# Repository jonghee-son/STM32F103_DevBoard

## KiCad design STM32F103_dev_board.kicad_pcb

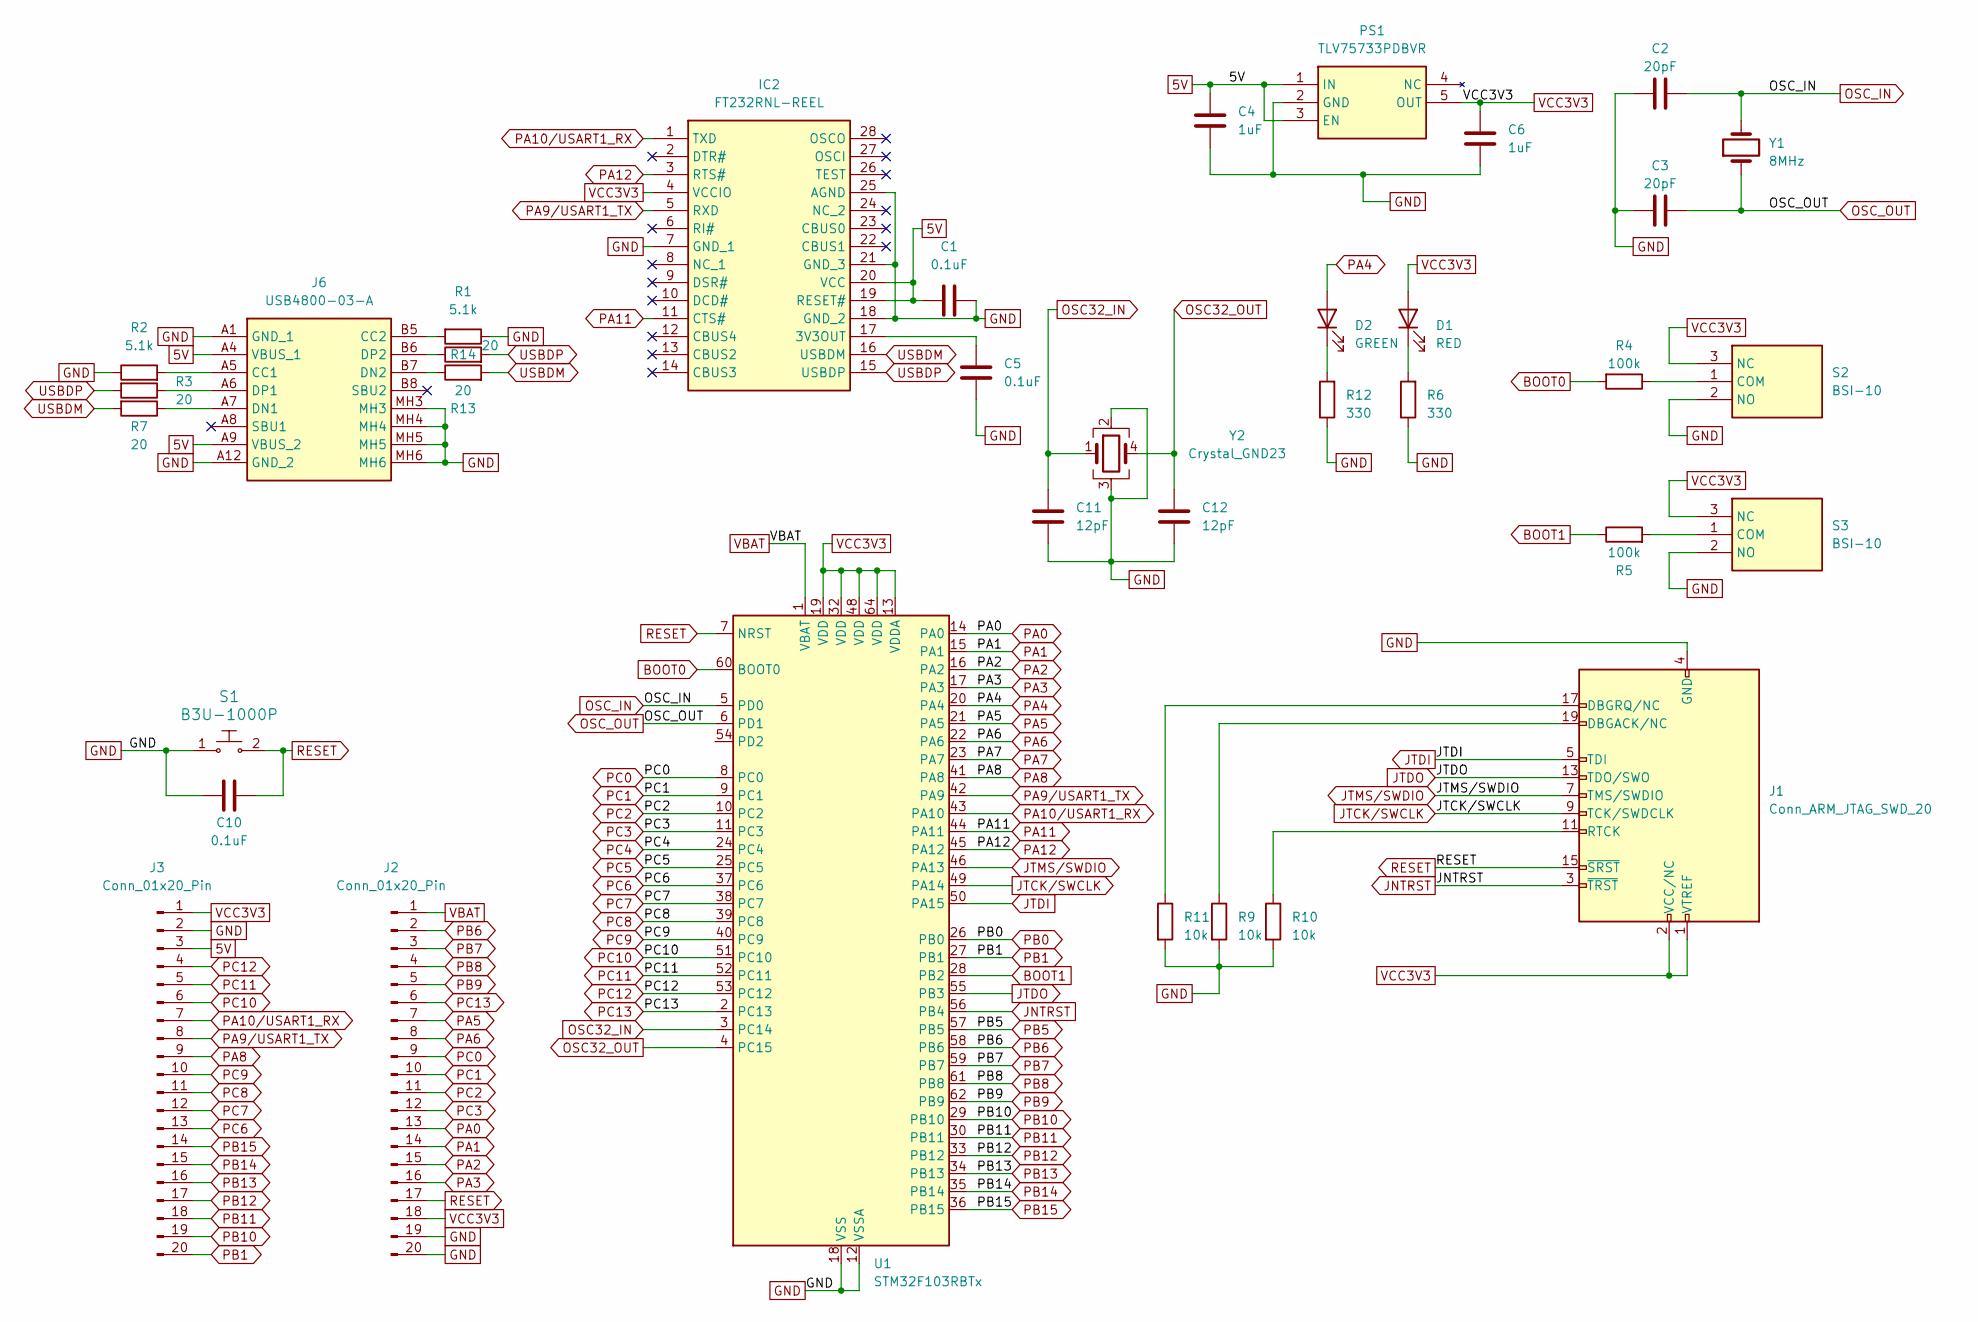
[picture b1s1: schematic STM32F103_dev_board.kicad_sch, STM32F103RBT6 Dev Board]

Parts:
C1, C5, C10: 0.1uF; C_0603_1608Metric_Pad1.08x0.95mm_HandSolder
C2, C3: 20pF; C_0603_1608Metric_Pad1.08x0.95mm_HandSolder
C4, C6: 1uF; C_0603_1608Metric_Pad1.08x0.95mm_HandSolder
C11, C12: 12pF; C_0603_1608Metric_Pad1.08x0.95mm_HandSolder
D1: RED; LED_0603_1608Metric_Pad1.05x0.95mm_HandSolder
D2: GREEN; LED_0603_1608Metric_Pad1.05x0.95mm_HandSolder
IC2: FT232RNL-REEL; SOP65P780X200-28N; Mouser Part Number 895-FT232RNL-REEL
J1: Conn_ARM_JTAG_SWD_20; IDC-Header_2x10_P2.54mm_Vertical
J2, J3: Conn_01x20_Pin; PinHeader_1x20_P2.54mm_Vertical
J6: USB4800-03-A; USB480003A; Mouser Part Number 640-USB4800-03-A
PS1: TLV75733PDBVR; SOT95P280X145-5N; Manufacturer_Part_Number TLV75733PDBVR; Mouser Part Number 595-TLV75733PDBVR
R1, R2: 5.1k; R_0603_1608Metric_Pad0.98x0.95mm_HandSolder
R3, R7, R13, R14: 20; R_0603_1608Metric_Pad0.98x0.95mm_HandSolder
R4, R5: 100k; R_0603_1608Metric_Pad0.98x0.95mm_HandSolder
R6, R12: 330; R_0603_1608Metric_Pad0.98x0.95mm_HandSolder
R9, R10, R11: 10k; R_0603_1608Metric_Pad0.98x0.95mm_HandSolder
S1: B3U-1000P; Switch_Tactile_SMD_B3U-1000P; MPN B3U-1000P; Digi-Key_PN SW1020CT-ND
S2, S3: BSI-10; BSI10; Manufacturer_Part_Number BSI-10
U1: STM32F103RBTx; LQFP-64_10x10mm_P0.5mm
Y1: 8MHz; Crystal_SMD_HC49-SD_HandSoldering
Y2: Crystal_GND23; Crystal_SMD_SeikoEpson_MC306-4Pin_8.0x3.2mm_HandSoldering

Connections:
5V: C1.2, C4.2, IC2.19 (RESET#), IC2.20 (VCC), J3.3, J6.A4 (VBUS_1), J6.A9 (VBUS_2), PS1.1 (IN), PS1.3 (EN)
BOOT0: R4.2, U1.60 (BOOT0)
BOOT1: R5.1, U1.28 (PB2)
GND: C1.1, C2.1, C3.1, C4.1, C5.1, C6.1, C10.2, C11.1, C12.1, IC2.7 (GND_1), IC2.18 (GND_2), IC2.21 (GND_3), IC2.25 (AGND), J1.4 (GND), J1.6 (GND), J1.8 (GND), J1.10 (GND), J1.12 (GND), J1.14 (GND), J1.16 (GND), J1.18 (GND), J1.20 (GND), J2.19, J2.20, J3.2, J6.A1 (GND_1), J6.A12 (GND_2), J6.MH3, J6.MH4, J6.MH5, J6.MH6, PS1.2 (GND), R1.1, R2.1, R6.1, R9.2, R10.2, R11.2, R12.1, S1.1, S2.2 (NO), S3.2 (NO), U1.12 (VSSA), U1.18 (VSS), U1.31 (VSS), U1.47 (VSS), U1.63 (VSS), Y2.2, Y2.3
JNTRST: J1.3 (~TRST), U1.56 (PB4)
JTCK/SWCLK: J1.9 (TCK/SWDCLK), U1.49 (PA14)
JTDI: J1.5 (TDI), U1.50 (PA15)
JTDO: J1.13 (TDO/SWO), U1.55 (PB3)
JTMS/SWDIO: J1.7 (TMS/SWDIO), U1.46 (PA13)
unnamed: D1.1 (K), R6.2
unnamed: D2.1 (K), R12.2
unnamed: C5.2, IC2.17 (3V3OUT)
unnamed: J1.19 (DBGACK/NC), R9.1
unnamed: J1.17 (DBGRQ/NC), R11.1
unnamed: J1.11 (RTCK), R10.1
unnamed: J6.A5 (CC1), R2.2
unnamed: J6.B5 (CC2), R1.2
unnamed: J6.A7 (DN1), R7.1
unnamed: J6.B7 (DN2), R13.1
unnamed: J6.A6 (DP1), R3.1
unnamed: J6.B6 (DP2), R14.1
unnamed: R4.1, S2.1 (COM)
unnamed: R5.2, S3.1 (COM)
OSC32_IN: C11.2, U1.3 (PC14), Y2.1
OSC32_OUT: C12.2, U1.4 (PC15), Y2.4
OSC_IN: C2.2, U1.5 (PD0), Y1.2
OSC_OUT: C3.2, U1.6 (PD1), Y1.1
PA0: J2.13, U1.14 (PA0)
PA1: J2.14, U1.15 (PA1)
PA2: J2.15, U1.16 (PA2)
PA3: J2.16, U1.17 (PA3)
PA4: D2.2 (A), U1.20 (PA4)
PA5: J2.7, U1.21 (PA5)
PA6: J2.8, U1.22 (PA6)
PA7: U1.23 (PA7)
PA8: J3.9, U1.41 (PA8)
PA9/USART1_TX: IC2.5 (RXD), J3.8, U1.42 (PA9)
PA10/USART1_RX: IC2.1 (TXD), J3.7, U1.43 (PA10)
PA11: IC2.11 (CTS#), U1.44 (PA11)
PA12: IC2.3 (RTS#), U1.45 (PA12)
PB0: U1.26 (PB0)
PB1: J3.20, U1.27 (PB1)
PB5: U1.57 (PB5)
PB6: J2.2, U1.58 (PB6)
PB7: J2.3, U1.59 (PB7)
PB8: J2.4, U1.61 (PB8)
PB9: J2.5, U1.62 (PB9)
PB10: J3.19, U1.29 (PB10)
PB11: J3.18, U1.30 (PB11)
PB12: J3.17, U1.33 (PB12)
PB13: J3.16, U1.34 (PB13)
PB14: J3.15, U1.35 (PB14)
PB15: J3.14, U1.36 (PB15)
PC0: J2.9, U1.8 (PC0)
PC1: J2.10, U1.9 (PC1)
PC2: J2.11, U1.10 (PC2)
PC3: J2.12, U1.11 (PC3)
PC4: U1.24 (PC4)
PC5: U1.25 (PC5)
PC6: J3.13, U1.37 (PC6)
PC7: J3.12, U1.38 (PC7)
PC8: J3.11, U1.39 (PC8)
PC9: J3.10, U1.40 (PC9)
PC10: J3.6, U1.51 (PC10)
PC11: J3.5, U1.52 (PC11)
PC12: J3.4, U1.53 (PC12)
PC13: J2.6, U1.2 (PC13)
RESET: C10.1, J1.15 (~SRST), J2.17, S1.2, U1.7 (NRST)
USBDM: IC2.16 (USBDM), R7.2, R13.2
USBDP: IC2.15 (USBDP), R3.2, R14.2
VBAT: J2.1, U1.1 (VBAT)
VCC3V3: C6.2, D1.2 (A), IC2.4 (VCCIO), J1.1 (VTREF), J1.2 (VCC/NC), J2.18, J3.1, PS1.5 (OUT), S2.3 (NC), S3.3 (NC), U1.13 (VDDA), U1.19 (VDD), U1.32 (VDD), U1.48 (VDD), U1.64 (VDD)

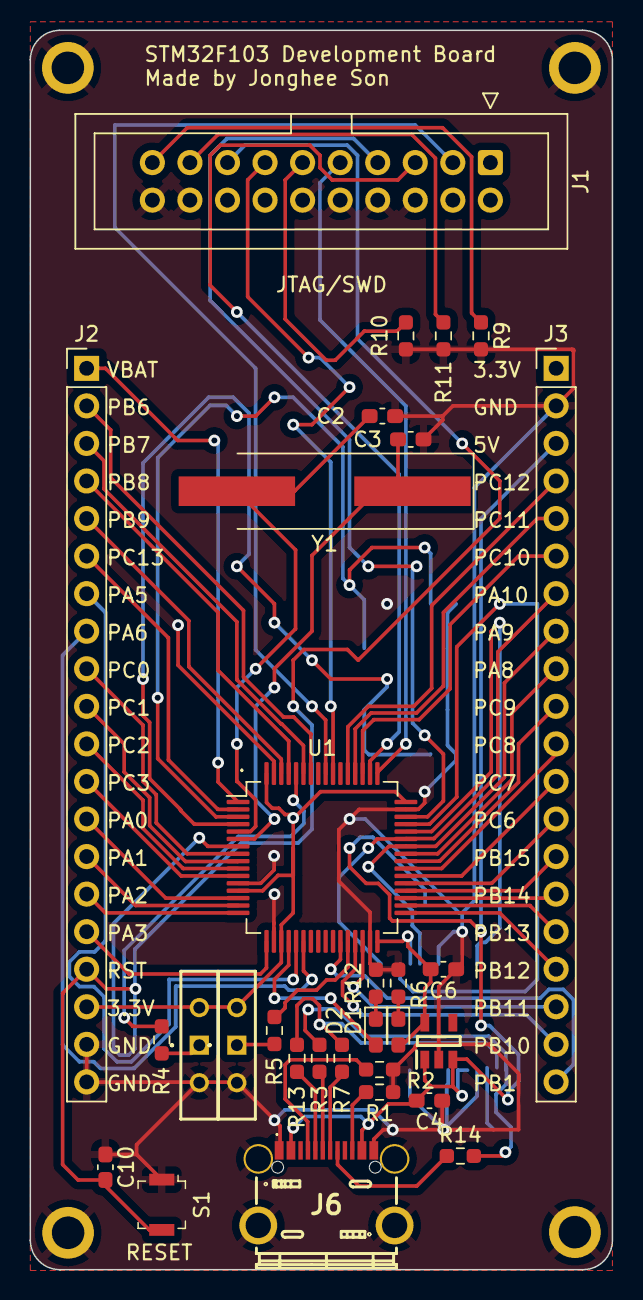
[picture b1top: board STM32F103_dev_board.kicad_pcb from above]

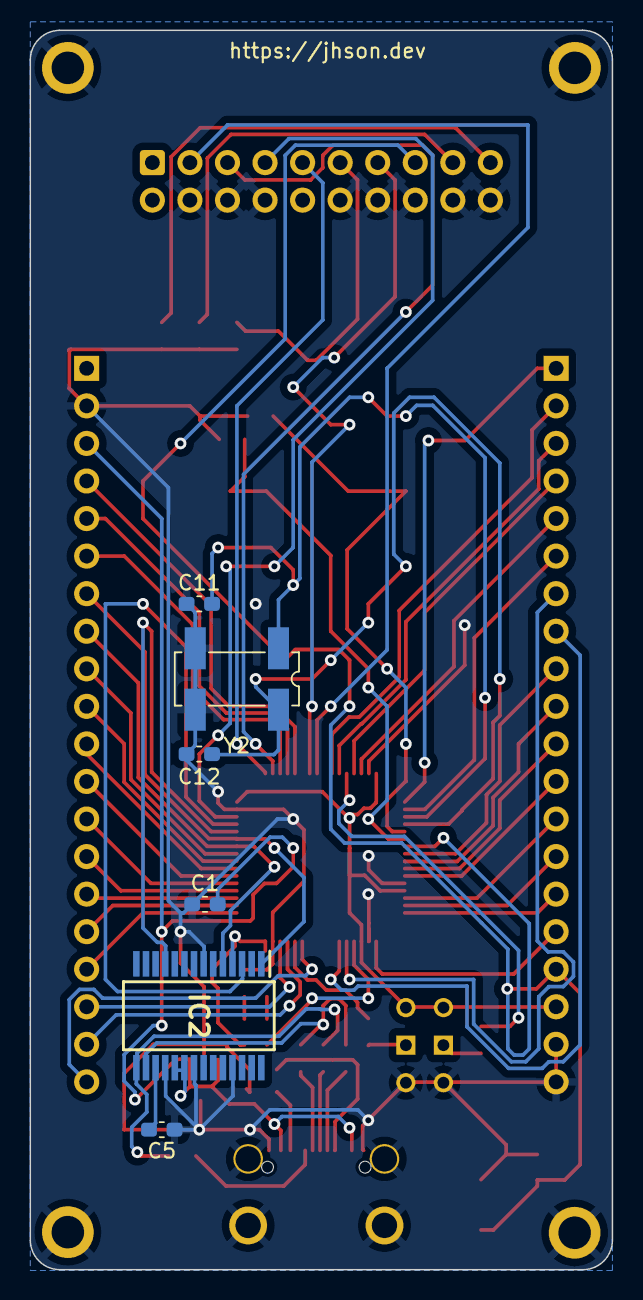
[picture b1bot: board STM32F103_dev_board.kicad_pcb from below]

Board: 4 copper layers, 39.4 x 83.8 mm, 36 parts (6 on the bottom side), 67 nets.

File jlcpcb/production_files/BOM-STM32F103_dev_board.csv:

Comment,Designator,Footprint,LCSC
Crystal_GND23,Y2,Crystal_SMD_SeikoEpson_MC306-4Pin_8.0x3.2mm_HandSoldering,C16320
20,"R13,R14",R_0603_1608Metric_Pad0.98x0.95mm_HandSolder,C22950
B3U-1000P,S1,Switch_Tactile_SMD_B3U-1000P,C231329
TLV70233DBVR,IC1,SOT95P280X145-5N,C26833
FT232RNL-REEL,IC2,SOP65P780X200-28N,C5246810
8MHz,Y1,Crystal_HC49-4H_Vertical,C718253
STM32F103RBTx,U1,LQFP-64_10x10mm_P0.5mm,C8735
1uF,C4,C_0603_1608Metric_Pad1.08x0.95mm_HandSolder,
330,R6,R_0603_1608Metric_Pad0.98x0.95mm_HandSolder,
20,R7,R_0603_1608Metric_Pad0.98x0.95mm_HandSolder,
5.1k,R2,R_0603_1608Metric_Pad0.98x0.95mm_HandSolder,
20pF,C3,C_0603_1608Metric_Pad1.08x0.95mm_HandSolder,
330,R12,R_0603_1608Metric_Pad0.98x0.95mm_HandSolder,
RED,D1,LED_0603_1608Metric_Pad1.05x0.95mm_HandSolder,
100k,R5,R_0603_1608Metric_Pad0.98x0.95mm_HandSolder,
0.1uF,C10,C_0603_1608Metric_Pad1.08x0.95mm_HandSolder,
GREEN,D2,LED_0603_1608Metric_Pad1.05x0.95mm_HandSolder,
Conn_02x03_Odd_Even,J4,PinHeader_2x03_P2.54mm_Vertical,
100k,R4,R_0603_1608Metric_Pad0.98x0.95mm_HandSolder,
Conn_ARM_JTAG_SWD_20,J1,IDC-Header_2x10_P2.54mm_Vertical,
1uF,C6,C_0603_1608Metric_Pad1.08x0.95mm_HandSolder,
20pF,C2,C_0603_1608Metric_Pad1.08x0.95mm_HandSolder,
10k,R10,R_0603_1608Metric_Pad0.98x0.95mm_HandSolder,
Conn_01x20_Pin,J3,PinHeader_1x20_P2.54mm_Vertical,
10k,R9,R_0603_1608Metric_Pad0.98x0.95mm_HandSolder,
20,R3,R_0603_1608Metric_Pad0.98x0.95mm_HandSolder,
10k,R11,R_0603_1608Metric_Pad0.98x0.95mm_HandSolder,
Conn_01x20_Pin,J2,PinHeader_1x20_P2.54mm_Vertical,
12pF,C12,C_0603_1608Metric_Pad1.08x0.95mm_HandSolder,
12pF,C11,C_0603_1608Metric_Pad1.08x0.95mm_HandSolder,
USB4800-03-A,J6,USB480003A,
5.1k,R1,R_0603_1608Metric_Pad0.98x0.95mm_HandSolder,
0.1uF,C5,C_0603_1608Metric_Pad1.08x0.95mm_HandSolder,
0.1uF,C1,C_0603_1608Metric_Pad1.08x0.95mm_HandSolder,

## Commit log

2023-09-15 Create LICENSE
2023-09-21 Added production files
2023-09-21 Changed USB C connector and fixed wiring to FT232RL
2023-09-22 Changed FT232RL into FT232RNL, fixed 32.768kHz crystal load capacitor
2023-09-22 Added board schematic
2023-09-22 Updated production files
2023-09-25 Small schematic fix
2023-10-13 Changed 0603 footprints to hand solderable ones
2023-10-13 Updated production files and schematic
2023-10-13 Fixed some labels and updated production files
2023-10-14 Removed external pull-up resistor in reset switch
2023-10-15 Changed net labels into global labels
2023-11-07 Added .gitignore
2023-11-17 changed LDO to TLV75733PDBVR
2023-11-28 Added silkscreen marking for gpio pins
2023-12-14 Changed boot mode selector to SPDT slide switch
2023-12-14 Changed my personal website URL on board silkscreen
2023-12-14 Moved R4 resistor position slightly
2023-12-15 Minor changes
2023-12-15 Changed direction of JTAG connector for easy connection
2023-12-15 Added copper pour for 1st & 2nd layer
2023-12-21 Changed 8MHz oscillator to SMD one
